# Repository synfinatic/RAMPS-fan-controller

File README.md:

# RAMPS v1.4 Fan and Analog Expansion Board

## Warning

This board is currently untested.  Manufacture & try at your own risk!

## What?

This board adds six (6) PWM controlled MOSFETs for controlling fans or LED's
and two analog inputs to your RAMPS v1.4 board.  It takes over the SERVOS and
AUX-1 ports on your RAMPS, leaving AUX-2 and AUX-3 available for other uses.

The board is designed to allow for +5-24V input to power your fans/LEDs/etc 
while the two analog connectors expose +5V from the RAMPS.

## Why?

I have a Flashforge Creator X (Makerbot Replicator 2X clone) with an additional
part cooling fan which I wanted to switch to using a RAMPS setup instead of the
rather outdated Mightyboard running Sailfish.  This printer supports dual extruders
so I wanted additional PWM controlled 24V outputs since the heated build plate and
hot ends would eat the 3 built into the RAMPS board.

Hence my config is:

 - Heated bulid plate: D8
 - E0 hot end: D9
 - E1 hot end: D10
 - E0 fan: D11 *
 - E1 fan: D6 *
 - Part cooling fan: D5 *
 - R channel on RGB Led: D4 *
 - G channel on RGB Led: D1 *
 - B channel on RGB Led: D0 *
 - E0 thermocouple amplifier: A4 *
 - E1 thermocouple amplifier: A3 *

* Notes connections to the expansion board

## Board Images

### Top

### Bottom

### 3D Rendering
(Note the pins for the SERVOS and AUX-1 should be female headers on th _bottom_ of the board!)

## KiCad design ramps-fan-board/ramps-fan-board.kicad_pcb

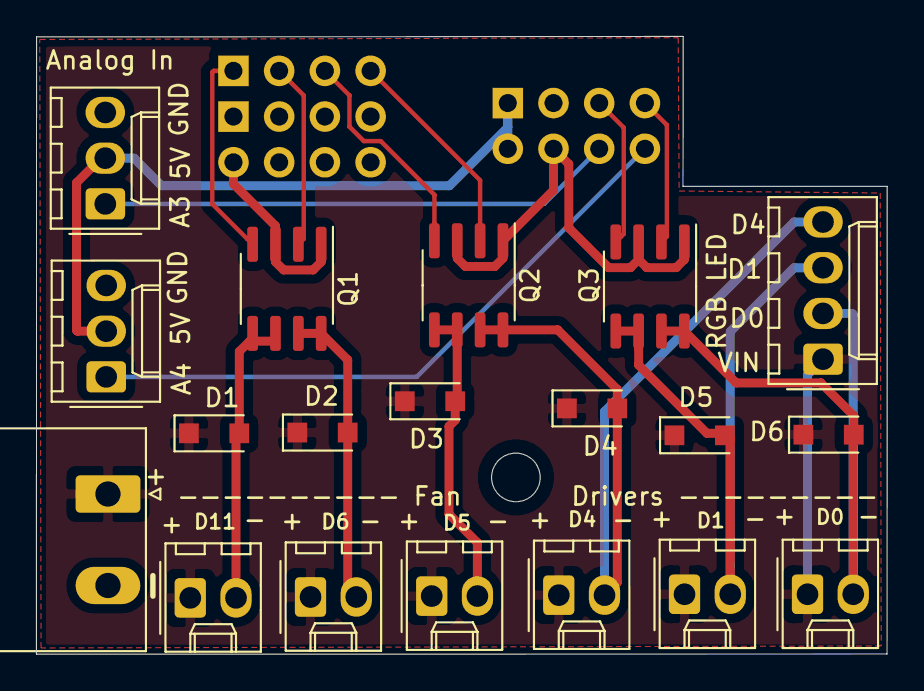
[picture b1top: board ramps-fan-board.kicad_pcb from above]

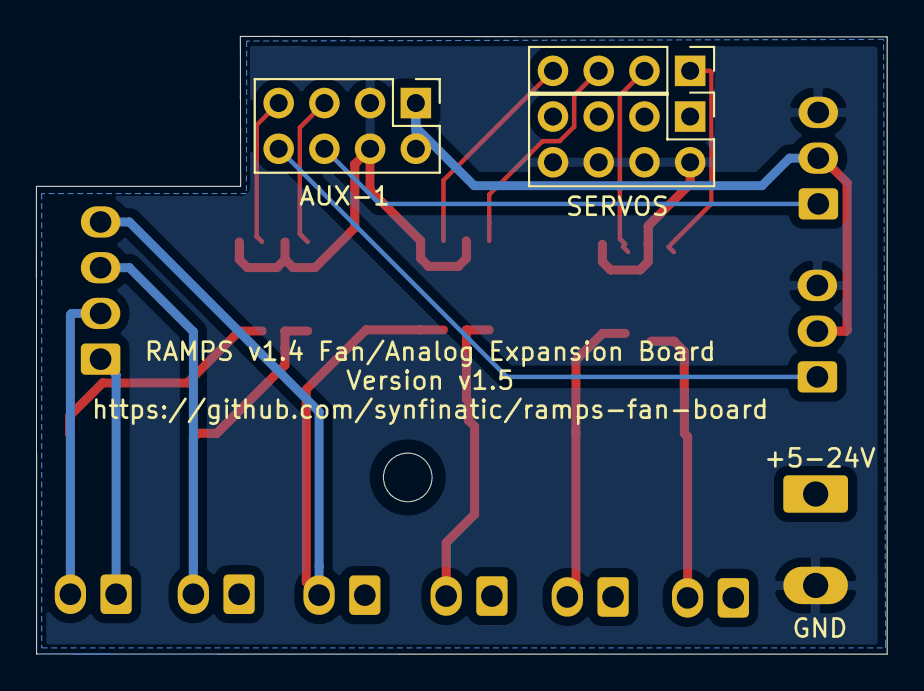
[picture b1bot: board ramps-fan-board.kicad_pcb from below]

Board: 2 copper layers, 47.3 x 34.3 mm, 22 parts (3 on the bottom side), 17 nets.

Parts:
D1, D2, D3, D4, D5, D6: 1N4148W; D_SOD-123F
J1: Screw_Terminal_01x02; PhoenixContact_MSTBA_2,5_2-G-5,08_1x02_P5.08mm_Horizontal
J2, J6: Conn_01x03; Molex_KK-254_AE-6410-03A_1x03_P2.54mm_Vertical
J3, J5: Conn_02x04_Top_Bottom; PinHeader_2x04_P2.54mm_Vertical-TopBottom
J4: Conn_01x04; PinHeader_1x04_P2.54mm_Vertical
J7, J8, J9, J10, J11, J12: Screw_Terminal_01x02; Molex_KK-254_AE-6410-02A_1x02_P2.54mm_Vertical
J13: Conn_01x04; Molex_KK-254_AE-6410-04A_1x04_P2.54mm_Vertical
Q1, Q2, Q3: AO4818B; SOIC-8_3.9x4.9mm_P1.27mm

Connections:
+5V: J2.2, J3.1, J3.5, J6.2
+24V: D1.1, D2.1, D3.1, D4.1, D5.1, D6.1, J1.1, J7.1, J8.1, J9.1, J10.1, J11.1, J12.1, J13.1
/A3: J2.1, J3.7
/A4: J3.8, J6.1
/D0: J3.4, Q3.2
/D1: J3.3, Q3.4
/D4: J4.4, Q2.2
/D5: J4.3, Q2.4
/D6: J4.2, Q1.2
/D11: J4.1, Q1.4
/OUT1: D1.2, J7.2, Q1.5, Q1.6
/OUT2: D2.2, J8.2, Q1.7, Q1.8
/OUT3: D3.2, J9.2, Q2.5, Q2.6
/OUT4: D4.2, J10.2, J13.4, Q2.7, Q2.8
/OUT5: D5.2, J11.2, J13.3, Q3.5, Q3.6
/OUT6: D6.2, J12.2, J13.2, Q3.7, Q3.8
GND: J1.2, J2.3, J3.2, J3.6, J5.5, J5.6, J5.7, J5.8, J6.3, Q1.1, Q1.3, Q2.1, Q2.3, Q3.1, Q3.3

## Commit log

2020-03-23 Initial Release v1.0
2020-03-24 v1.5 (untested)
    Still waiting on the v1.0 PCB's back for testing, but updated things
    anyways.
    - Add dedicated RGB 4 pin header
    - Add Power plane on top of board
    - Move SERVOS and AUX-1 parts to the back of the board
    - Updated pin outs to correspond to flipping the parts
